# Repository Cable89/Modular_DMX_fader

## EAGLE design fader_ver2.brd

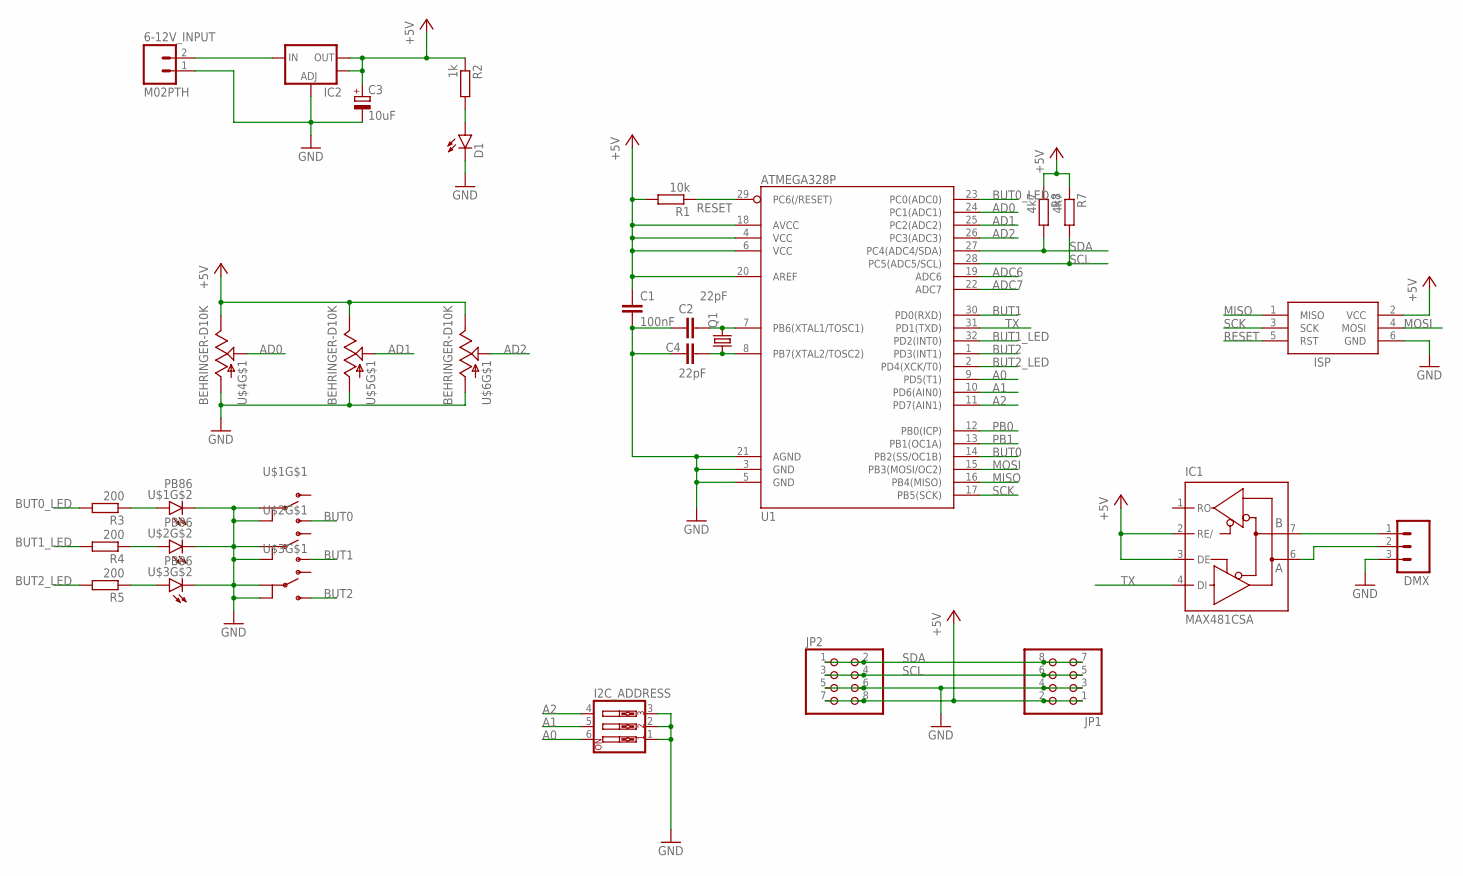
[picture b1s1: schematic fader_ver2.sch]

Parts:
6-12V_INPUT: M02PTH; 1X02
C1: 100nF; C0603
C2, C4: 22pF; C0603
C3: 10uF; CT6032
D1: LED; LED-3528MM
DMX: M03PTH; 1X03
I2C_ADDRESS: SW_DIP-3; EDG-03
IC1: MAX481CSA; SO08
IC2: V_REG_LM1117SOT223; SOT223
ISP: AVRISP-6; AVRISP
JP1, JP2: PINHD-2X4/90; 2X04/90
Q1: CRYSTALHC49UP; HC49UP
R1: 10k; R0603
R2: 1k; R0603
R3, R4, R5: 200; R0603
R7, R8: 4k7; R0603
U1: ATMEGA328P; TQFP32-08
U$1, U$2, U$3: PB86
U$4, U$5, U$6: BEHRINGER-D10K; BEHRINGER_D10K

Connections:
A0: I2C_ADDRESS.6, U1.9 (PD5(T1))
A1: I2C_ADDRESS.5, U1.10 (PD6(AIN0))
A2: I2C_ADDRESS.4, U1.11 (PD7(AIN1))
AD0: U1.24 (PC1(ADC1)), U$4.P$2 (2)
AD1: U1.25 (PC2(ADC2)), U$5.P$2 (2)
AD2: U1.26 (PC3(ADC3)), U$6.P$2 (2)
ADC6: U1.19 (ADC6)
ADC7: U1.22 (ADC7)
BUT0: U1.14 (PB2(SS/OC1B)), U$1.2 (NO)
BUT0_LED: R3.2, U1.23 (PC0(ADC0))
BUT1: U1.30 (PD0(RXD)), U$2.2 (NO)
BUT1_LED: R4.2, U1.32 (PD2(INT0))
BUT2: U1.1 (PD3(INT1)), U$3.2 (NO)
BUT2_LED: R5.2, U1.2 (PD4(XCK/T0))
GND: 6-12V_INPUT.1, C1.2, C2.1, C3.-, C4.1, D1.C, DMX.3, I2C_ADDRESS.1, I2C_ADDRESS.2, I2C_ADDRESS.3, IC1.5 (GND), IC2.1 (ADJ), ISP.6 (GND), JP1.3, JP1.4, JP2.5, JP2.6, U1.3 (GND), U1.5 (GND), U1.21 (AGND), U$1.1_1 (IN1), U$1.1_2 (IN2), U$1.L3 (C), U$2.1_1 (IN1), U$2.1_2 (IN2), U$2.L3 (C), U$3.1_1 (IN1), U$3.1_2 (IN2), U$3.L3 (C), U$4.P$3 (3), U$5.P$3 (3), U$6.P$3 (3)
MISO: ISP.1 (MISO), U1.16 (PB4(MISO))
MOSI: ISP.4 (MOSI), U1.15 (PB3(MOSI/OC2))
unnamed: 6-12V_INPUT.2, IC2.3 (IN)
unnamed: DMX.1, IC1.7 (B)
unnamed: DMX.2, IC1.6 (A)
unnamed: C2.2, Q1.2, U1.7 (PB6(XTAL1/TOSC1))
unnamed: C4.2, Q1.1, U1.8 (PB7(XTAL2/TOSC2))
unnamed: D1.A, R2.2
unnamed: R3.1, U$1.L2 (A)
unnamed: R4.1, U$2.L2 (A)
unnamed: R5.1, U$3.L2 (A)
PB0: U1.12 (PB0(ICP))
PB1: U1.13 (PB1(OC1A))
RESET: ISP.5 (RST), R1.1, U1.29 (PC6(/RESET))
SCK: ISP.3 (SCK), U1.17 (PB5(SCK))
SCL: JP1.5, JP1.6, JP2.3, JP2.4, R7.2, U1.28 (PC5(ADC5/SCL))
SDA: JP1.7, JP1.8, JP2.1, JP2.2, R8.2, U1.27 (PC4(ADC4/SDA))
TX: IC1.4 (DI), U1.31 (PD1(TXD))
VCC: C1.1, C3.+, IC1.2 (RE/), IC1.3 (DE), IC1.8 (VCC), IC2.2 (OUT), IC2.4 (OUT), ISP.2 (VCC), JP1.1, JP1.2, JP2.7, JP2.8, R1.2, R2.1, R7.1, R8.1, U1.4 (VCC), U1.6 (VCC), U1.18 (AVCC), U1.20 (AREF), U$4.P$5 (1), U$5.P$5 (1), U$6.P$5 (1)

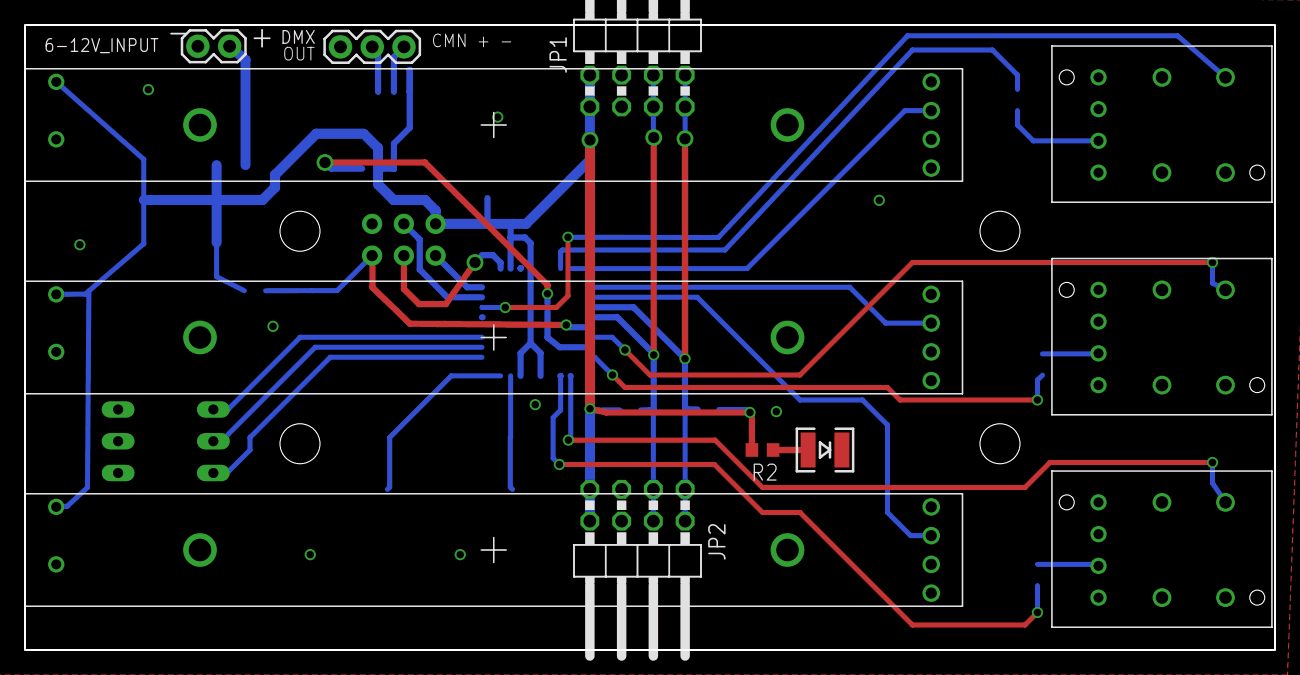
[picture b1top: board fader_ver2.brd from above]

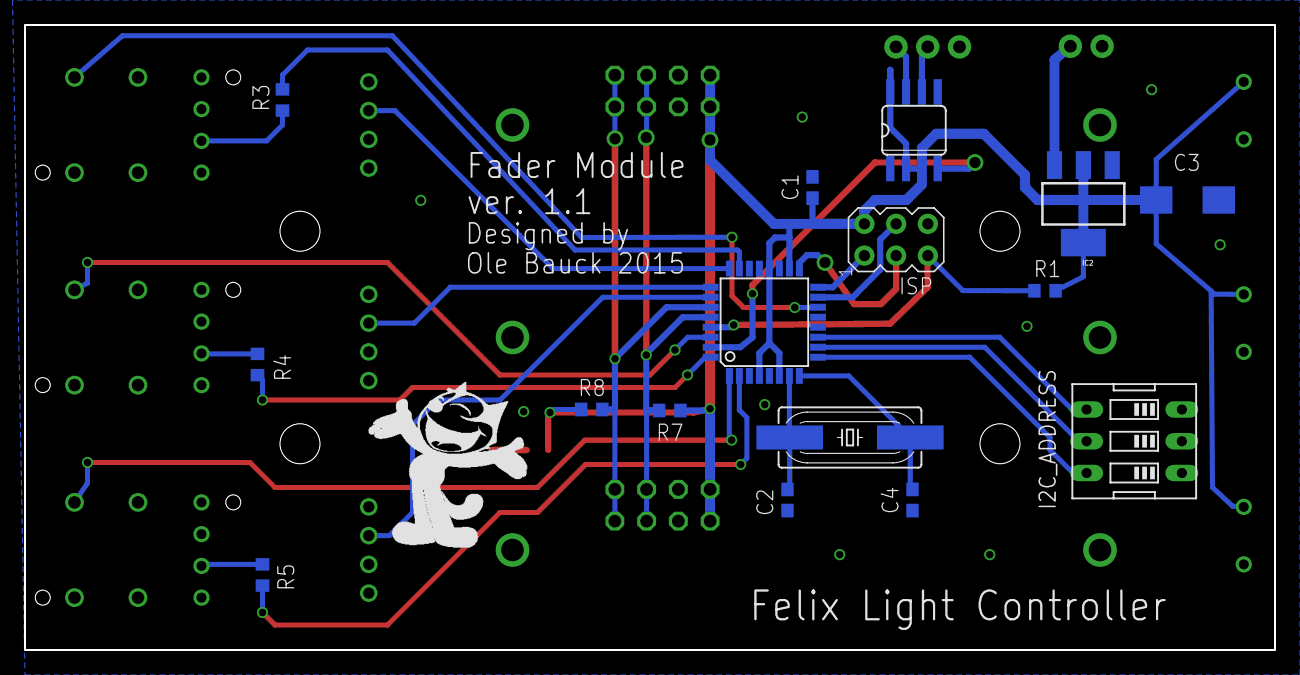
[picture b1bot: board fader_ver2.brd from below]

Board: 2 copper layers, 100.0 x 50.0 mm, 29 parts (17 on the bottom side), 30 nets.

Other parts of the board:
U$7: FELIX

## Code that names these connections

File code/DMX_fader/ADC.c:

/*
 * ADC.c
 *
 * Created: 12.10.2013 18:27:59
 *  Author: Ole
 */ 

#include "ADC.h"
#include "DMX_transmit.h"
#include "TWI_slave.h"
#include "HysteresisFilter.h"
#include <avr/interrupt.h>

#define BUT0_LED PC0
#define BUT1_LED PD2
#define BUT2_LED PD4

#define BUT0 PB2
#define BUT1 PD0
#define BUT2 PD3

volatile uint8_t counter = 1;
volatile uint8_t input_buffer[4] = {0, 0, 0, 0};

void leds_and_buttons_init()
{
	//leds
	DDRC |= (1<<BUT0_LED);
	DDRD |= (1<<BUT1_LED) | (1<<BUT2_LED);
	
	PORTC &= ~(1<<BUT0_LED);
	PORTD &= ~((1<<BUT1_LED) | (1<<BUT2_LED));
	//PORTC |= (1<<BUT0_LED);
	//PORTD |= (1<<BUT1_LED) | (1<<BUT2_LED);
	
	//buttons
	DDRD &= ~((1<<BUT1) | (1<<BUT2));
	DDRB &= ~(1<<BUT0);
	//pullup
	PORTD |= (1<<BUT1) | (1<<BUT2);
	PORTB |= (1<<BUT0);
}

void adc_init()
{
	DDRC &= ~((1<<PC1) | (1<<PC2) | (1<<PC3));
	//PORTC |= (1<<PC1) | (1<<PC2) | (1<<PC3);
	//ADC1, AREF, left adjust 
	ADMUX = counter | (1<<ADLAR);		
	//enable, start conversion, interrupt enable, XTAL divide by 128 => 16Mhz/128 = 125 KHz
	ADCSRA |= (1<<ADEN) | (1<<ADSC) | (1<<ADIE) | (1<<ADPS2) | (1<<ADPS1) | (1<<ADPS0);
																						
	sei();
}


ISR(ADC_vect)
{
	input_buffer[counter - 1] = hysteresisfilter((uint16_t)((ADCH << 2) /*| (ADCL >> 6)*/), input_buffer[counter-1]);
	DmxField[counter - 1] = input_buffer[counter -1];
	
	
	if (PINB & (1<<BUT0))
	{
		PORTC |= (1<<BUT0_LED);
		DmxField[0] = 255;
	}
	else
	{
		PORTC &= ~(1<<BUT0_LED);
	}
	
	if (PIND & (1<<BUT1))
	{
		PORTD |= (1<<BUT1_LED);
		DmxField[1] = 255;
	}
	else
	{
		PORTD &= ~(1<<BUT1_LED);
	}
	
	if (PIND & (1<<BUT2))
	{
		PORTD |= (1<<BUT2_LED);
		DmxField[2] = 255;
	} 
	else
	{
		PORTD &= ~(1<<BUT2_LED);
	}
	
	counter++;
	
	if (counter > 3)
	{
		counter = 1;
		input_buffer[3] = (uint8_t)(((PINB & (1<<BUT0)) >> BUT0) | (((PIND & (1<<BUT1)) >> BUT1) << 1) | (((PIND & (1<<BUT2)) >> BUT2) << 2));
		TWI_update_buffer(input_buffer, 4);
	}
	//choose next channel
	ADMUX = counter | (1<<ADLAR);
	
	//start new conversion
	ADCSRA |= (1<<ADSC);
}

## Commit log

2019-11-17 Imported project to KiCAD
2019-11-26 Made frontplates for eurorack
2019-12-09 Generated DXF
2019-12-09 Modified button hole size, added slots for faders
2019-12-09 Increased height of button hole by 0.5mm, decreased length of slider slot by 0.8mm
2019-12-09 Increased height of button hole by 0.5mm
2019-12-09 Frontplate for enkeltstående fader
2019-12-09 Increased height of panel to account for fader knob
2019-12-09 Made bunnplate template
2020-09-17 Want to send button data as well
2020-09-17 Message buffer lenght +1 to send button data as well
2020-09-17 Working with slave
2020-09-17 Added hysteresis filter to filter slider input
2020-09-17 Error in initialization
2020-09-17 Made separate buffer for TWI data to include buttons. Added filter on slider data
2020-09-17 Code for arduino addon to add USB MIDI support
2020-09-17 Atmel studio project file...
2020-09-17 Ignore all generated files except hex
2020-09-22 Drawn box to be cut from steel
2020-09-22 Variant without USB-C slot
2020-09-26 Made 40HP panelø
2020-09-26 Redone 20 and 40HP from 10HP
2020-09-26 Sideplate
2020-09-26 M4 not M3
2020-09-26 Sidepanel
2020-09-26 Adjusted size after test cut
2020-09-27 Bunnplate
2020-09-27 Adjusted size
2020-10-26 Added autohotkey MIDI to volume control script
2020-10-26 Read twi address from dip switch
2020-10-26 defines for reading twi address from dip switch
2020-10-26 Send different note per button, and send vel=0 on falling edge
2020-11-18 Esc should not exit app
2020-11-18 variant of script uising a different midi libary
2020-11-18 Tests for midi_in.dll
2020-11-18 Added license for Midi.ahk
2025-03-19 Uncommited local changes

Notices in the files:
parts and their libraries:
SparkFun-PowerIC: Licensing: Creative Commons ShareAlike 4.0 International - https://creativecommons.org/licenses/by-sa/4.0
